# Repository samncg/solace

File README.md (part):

# Solace

A pocket-sized, battery-powered **hi-fi music player** built around the Raspberry Pi
**RP2350B**. Music files live on a microSD card, decode on the MCU, and go out through a
**PCM5102A** DAC and a **TPA6132A2** capless headphone amplifier to a 3.5 mm jack. A
2.83″ 200×648 SPI TFT shows the UI, a **DRV2605L** drives haptics, and an IMU, a magnetic
encoder and six buttons provide input. A **PCF8563TS** real-time clock keeps time on a
coin cell, and an **I²S MEMS microphone** supports capture and voice-driven mini-games.

This document is the project's single source of truth for **what the hardware is, how it
is put together, and what is still open**.

- **Status:** schematic complete and netlist-verified. **Board outline drafted, no placement yet.**
- **EDA:** KiCad 10.0
- **Intended build:** single-sided PCB (see [§14](#14-known-limitations--open-items))

---

## 1. Scope

**In scope**

- Portable, battery-powered audio playback (local files on microSD).
- 2.83″ colour display with software-adjustable brightness.
- Wired headphone/earbud output.
- Haptic feedback, motion sensing, rotary navigation (magnetic encoder), 6 tactile buttons.
- I²S MEMS microphone for capture and mini-games.
- Real-time clock with CR1220 backup (SMT holder, single-sided assembly).
- USB-C charging with power-path so the device runs while charging.
- Firmware-visible battery voltage, battery temperature, and charger state.

**Out of scope / not present**

- No speaker, no Bluetooth/Wi-Fi (no radio of any kind).
- No software in this repository — this is the hardware design only.
- No PCB layout beyond the drafted 100 × 64 mm outline (see [§14](#14-known-limitations--open-items)).

---

## 2. Repository layout

| Path | Contents |
|---|---|
| `main.kicad_sch` | The complete schematic (single flat sheet) |
| `main.kicad_pro` | KiCad project settings |
| `main.txt` | Netlist, `kicadsexpr` format — **generated**, do not hand-edit |
| `main.csv` | BOM — **generated/curated**, grouped by value + footprint |
| `main.kicad_pcb` | **Board file: 100 × 64 mm outline, 4-layer stackup.** No placement or routing yet |
| `docs/Solace_Hardware_Design_Documentation_RevB.pdf` | Design documentation package: architecture, electrical specification, interfaces, BOM appendix and the schematic as an A2 fold-out |
| `tools/build_docs.py` | Regenerates that PDF from `main.csv`, `main.txt` and `main.kicad_sch` |
| `libs/lcsc/` | Imported LCSC symbols, footprints and 3D models |
| `ganyu.kicad_sym`, `ganyu.kicad_mod` | Local custom symbol/footprint library |
| `docs/datasheets/rp2350/` | RP2350 datasheet + *Hardware design with RP2350* |
| `docs/datasheets/panels/` | Panel datasheets (C14 14-pin, H12 12-pin, CON8 8-pin variants) |
| `docs/mechanical/` | Enclosure sketch (`rough-sketch.png`, `.pdn`) |
| `fabrication/jlcpcb/` | JLCPCB fabrication output and project database |
| `fabrication/gerbers/` | Gerber and drill export plus job file |
| `backups/` | Manual schematic snapshots, earlier BOM/netlist, superseded PDFs |
| `backups/kicad-autosave/` | Timestamped KiCad auto-backup ZIPs |
| `backups/stray-main.kicad_pcb/` | Archived stray folder that previously shadowed the board filename |

> `main.kicad_pcb` currently contains **only the board outline** (Edge.Cuts, 100 × 64 mm,
> 3 mm corner radius) plus the 4-layer stackup. It has no footprints, so the first
> *Update PCB from Schematic* will drop in all 159 parts cleanly.

---

## 3. System architecture

```mermaid
graph TD
    USB["USB-C 16P<br/>CC 5.1k, USBLC6 ESD, 1.1A fuse"]
    CHG["TP4056 charger<br/>500 mA, CHRG#/STDBY# to MCU"]
    PROT["DW01A + FS8205A<br/>cell protection (BAT-)"]
    CELL["Li-ion cell<br/>JST-PH CN2"]
    LS["Load sharing<br/>D1 Schottky + Q4 PMOS"]
    VSYS["VSYS rail"]
    LDO1["AP2112K-3.3<br/>600 mA"]
    LDO2["TPS7A2033<br/>300 mA low-noise"]
    V3["+3V3 digital"]
    V3A["AUDIO_3V3"]
    MCU["RP2350B<br/>QFN-80"]
    FLASH["W25Q128JV<br/>16 MB QSPI flash"]
    PSRAM["APS6404L<br/>8 MB QSPI PSRAM"]
    SD["microSD<br/>TF-01A"]
    LCD["2.83in 200x648 TFT<br/>GC9B72, 4-wire SPI"]
    BL["Backlight<br/>Q2 + R35 3.3R, PWM"]
    DAC["PCM5102A<br/>I2S DAC"]
    AMP["TPA6132A2<br/>capless HP amp"]
    JACK["3.5 mm TRS jack"]
    HAP["DRV2605L<br/>haptics"]
    IMU["LSM6DSO<br/>IMU"]
    ENC["AS5600<br/>magnetic encoder"]
    EXP["TCA9554<br/>I2C GPIO expander"]
    BTN["6 buttons<br/>UP/DOWN/LEFT/RIGHT/A/B"]
    RTC["PCF8563TS<br/>I2C RTC + CR1220 backup"]
    MIC["I2S MEMS mic"]

    USB --> CHG
    USB -->|VSYS via D1| VSYS
    CHG --> CELL
    CELL --- PROT
    CELL -->|via Q4| VSYS
    VSYS --> LDO1 --> V3
    VSYS --> LDO2 --> V3A
    V3 --> MCU
    V3 --> FLASH
    V3 --> PSRAM
    V3 --> SD
    V3 --> LCD
    V3 --> HAP
    V3 --> IMU
    V3 --> ENC
    V3 --> EXP
    V3 --> RTC
    V3A --> DAC --> AMP --> JACK
    MCU <--> FLASH
    MCU <--> PSRAM
    MCU <--> SD
    MCU -->|SPI1| LCD
    MCU -->|PWM| BL
    MCU -->|I2S| DAC
    MCU <-->|I2C0| HAP
    MCU <-->|I2C0| IMU
    MCU <-->|I2C0| ENC
    MCU <-->|I2C0| EXP
    MCU <-->|I2C0| RTC
    MCU <-->|I2S PIO| MIC
    EXP --> BTN
```

---

## 4. Compute, memory, clock

| Item | Part | Notes |
|---|---|---|
| MCU | **RP2350B** (QFN-80), LCSC `C42415655` | All GPIOs 0–47 available |
| Program flash | **W25Q128JVSIQ** 128 Mbit (16 MB) QSPI, `U17` | Shares the QSPI bus |
| PSRAM | **APS6404L-3SQR** 64 Mbit (8 MB) QSPI, `U1` | Chip-select on **GPIO0** (`XIP_CS1n`), separate from flash CS |
| Crystal | **ABM8-272-T3** (12 MHz), `U18` | The Pico/Pico 2 crystal; 15 pF load caps `C61`/`C62`, 1 kΩ series `R23` |
| Core supply | RP2350 internal buck | 3.3 µH `AOTA-B201610S3R3-101-T` (`L10`) → `+1V1`, `C58` 10 µF + `C59` 1 µF |
| Regulator analog supply | `VREG_AVDD` | 33 Ω (`R41`) + 4.7 µF (`C60`), per the RP2350 reference design |

The core-rail network (inductor part number, `VREG_AVDD` RC filter) is copied **exactly**
from *Hardware design with RP2350* — including the Abracon inductor, which is a polarised
part. **Layout note:** the inductor's polarity dot must be oriented as in the reference
design, or regulator instability results.

**Debug:** `J3`, 3-pin SWD header (SWDIO/SWCLK/GND) + `SW12` BOOTSEL + `SW11` RUN.

---

## 5. Power

### 5.1 Topology

```
USB-C ──F3 1.1A──┬── TP4056 (U2) ──► BAT+ ──► cell (CN2)
                 │        │
                 │        └──► DW01A + FS8205A protection in the BAT- path
                 │
                 └──D1 (B5819WS)──► VSYS ◄──Q4 (AO3401A)── BAT+
                                       │
                                       ├── AP2112K-3.3 (U4) ──► +3V3  (digital)
                                       └── TPS7A2033 (U5)  ──► AUDIO_3V3 (audio)
```

### 5.2 Charger

| Parameter | Value |
|---|---|
| Charger | **TP4056** (`U2`), ESOP-8 |
| Charge current | **500 mA** (`R5` = 2.4 kΩ, I = 1200/R) |
| `CE` | Driven by `CHARGE_EN` (see below) |
| `CHRG#` | → **GPIO18**, 10 kΩ pull-up `R13`. Active-low: charging in progress |
| `STDBY#` | → **GPIO22**, 10 kΩ pull-up `R49`. Active-low: charge complete |
| `TEMP` | Tied to GND — the TP4056's own thermal cut-out is **disabled** |

### 5.3 Load sharing (power path)

`BAT+` feeds only the cell, the protection FETs, the charger and the fuel-gauge divider.
The system is fed from **`VSYS`**, which is whichever of USB or battery is present:

| Ref | Part | Role |
|---|---|---|
| `D1` | B5819WS Schottky | USB → `VSYS`, blocks battery back-feed into the USB port |
| `Q4` | AO3401A PMOS | `BAT+` → `VSYS`; **source on `VSYS`, drain on `BAT+`** so the body diode can never let USB charge the cell |
| `R44` | 100 Ω | Gate pull-up to `USB_5V` |
| `R45` | 100 kΩ | Gate pull-down |
| `C66` | 22 µF | `VSYS` bulk |
| `C67` | 10 µF | `BAT+` / charger output |

Behaviour: USB present → gate ≈ 5 V vs. a 4.65 V source, Vgs ≈ +0.35 V → **Q4 off**, cell
disconnected from the load, charger termination works correctly. USB absent → gate 0 V,
Vgs = −V<sub>BAT</sub> → **Q4 on**.

### 5.4 Regulators

| Rail | Regulator | Load |
|---|---|---|
| `+3V3` | AP2112K-3.3 (`U4`), 600 mA | MCU I/O, flash, PSRAM, SD, display, backlight, haptics, sensors, expander |
| `AUDIO_3V3` | TPS7A2033 (`U5`), 300 mA, low-noise | DAC + amplifier |

`AUDIO_3V3` is split per domain through ferrites `L5`–`L8` into the PCM5102A's `AVDD`,
`CPVDD`, `DVDD` and the amplifier's `VDD`.

**Power switch:** `SW5` (slide) connects `VSYS` to `LDO_ENABLE`, which drives both
regulators' `EN` pins; `R10` (100 kΩ) holds them off when the switch is open. The
regulators' inputs are always live, so only their quiescent current is drawn when "off".

### 5.5 Charger control (firmware)

`CE` is not tied to USB — firmware can stop charging:

```
USB_5V ──R47 10k──┬── U2.CE
                  └── Q5.D (AO3400A)   S → GND
                       G ──R48 100k── GND
                       G ── CHARGE_CTL ── GPIO21
```

| State | `CHARGE_CTL` | Q5 | `CE` | Charging |
|---|---|---|---|---|
| MCU off / power switch open | floating | off (R48) | 5 V via R47 | **enabled** |
| Boot, before init | high-Z | off | 5 V | **enabled** |
| Allow | driven low | off | 5 V | enabled |
| Cut | driven high | on | 0 V | **disabled** |

Fail-safe by construction: a dead MCU or a hung boot can never leave the device unable to
charge. The MCU pin only drives a gate, so 5 V never reaches the RP2350.

### 5.6 Battery monitoring

| Quantity | Sense | Notes |
|---|---|---|
| Pack voltage | `R24` 220 k / `R28` 100 k → **GPIO40 / ADC0**, `C25` 100 nF | 4.2 V → 1.31 V |
| Cell temperature | `J2` external NTC + `R46` 10 k to `+3V3`, `C68` 100 nF → **GPIO44 / ADC4** | 10 k NTC, B = 3950 |

Temperature is referenced to the regulated `+3V3`, so it reads correctly **whether or not
USB is connected**. The NTC is **off-board** (`J2`): it must be bonded to the cell, not
mounted on the PCB, and the 100 nF at the connector keeps the ADC stable over the lead
length.

---

## 6. Display

| Item | Value |
|---|---|
| Panel | **ZJY283-2064KIWPG03-C14** — 2.83″, 200×648, normally black, all-view |
| Driver IC | **GC9B72** |
| Interface | 4-wire SPI (write-only — no SDO, no TE on this variant) |
| Connector | `U9` **KH-FG0.5-H2.0-14P-SMT**, 14-pin 0.5 mm FPC, H = 2.0 mm, LCSC `C5441651` |
| FPC | 0.5 mm pitch, `PI+FPC = 0.3 ± 0.03 mm` |

| Panel pin | Signal | MCU |
|---|---|---|
| 1 | GND | — |
| 2 | RESET | GPIO7 |
| 3 | SCL | **GPIO10** (SPI1 SCK) |
| 4 | D/C | GPIO8 |
| 5 | CS | **GPIO9** (SPI1 CSn) |
| 6 | SDA | **GPIO11** (SPI1 TX) |
| 7 | NC | — |
| 8 | GND | — |
| 9 | VDD | `+3V3` |
| 10 | LEDK | backlight cathode |
| 11, 12 | GND | — |
| 13, 14 | NC | — |

SPI mode **0 or 3** (the panel latches SDA on the SCL rising edge). CS and RESET are
active-low. Hardware `SPI1` is used for all three of SCK/MOSI/CS.

**Local decoupling:** `C63` 1 µF at the panel's VDD pin.

### 6.1 Backlight

`+3V3` → (LED anodes, tied internally to VDD) → LEDK → `R35` **3.3 Ω** → `Q2` (AO3400A,
low-side) → GND. Gate on **GPIO6**, pulled down by `R36` 10 kΩ (default off).

Brightness is **PWM on GPIO6** — GPIO6's alternate function 4 is **PWM3 A**, so a hardware
PWM slice drives the gate directly. Use 10–20 kHz; average LED current ≈ duty × ~95 mA.

> **Backlight limitation — please read §14.1.** The C14 variant has **no LEDA pin**; the
> LED anodes are internally tied to VDD, so the string only ever sees 3.3 V against a
> V<sub>F</sub> of ≈3.0–3.2 V. Rated brightness (120 mA / 350 cd/m²) is **not reachable**
> from this rail.

---

## 7. Audio

```
RP2350 I2S ──► PCM5102A (U6) ──470R──► TPA6132A2 (U11) ──► PJ-342 jack (CN1)
 BCK  GPIO3      2.1 Vrms line out      capless, charge pump      3.5 mm TRS
 DIN  GPIO2                             G0/G1 = 0 (−6 dB)
 LRCK GPIO4
 XSMT GPIO42 (10k pull-down, starts muted)
 EN   GPIO43 (10k pull-down, starts off)
```

| Item | Value |
|---|---|
| DAC | **PCM5102A** (`U6`), I²S, 2.1 V<sub>rms</sub> |
| `SCK` (pin 12) | Tied to GND → internal clock derived from BCK |
| Charge pump | `C21` 2.2 µF across CAPP/CAPM, `C20` 2.2 µF on VNEG |
| Amp | **TPA6132A2** (`U11`), capless (integrated charge pump) |
| Amp supply | `AUDIO_3V3` via ferrite `L8` |
| Jack | **PJ-342** (`CN1`), 3.5 mm TRS |
| Rail | `AUDIO_3V3` from the low-noise TPS7A2033 |

**Jack wiring:** `CN1.2`/`CN1.5` = GND (sleeve tabs), `CN1.3` = right, `CN1.6` = left,
`CN1.4`/`CN1.7` = switch contacts (unused). Pad geometry is consistent with this, but the
symbol has generic pin names — **confirm TIP/RING with a continuity test** on a real part.

**Loudness:** comfortable. ~0.6 V<sub>rms</sub> into 16–32 Ω is ≈110–119 dB SPL on typical
earbuds. At the fixed −6 dB gain the DAC's 2.1 V<sub>rms</sub> becomes ≈1.05 V<sub>rms</sub>,
close to the TPA6132A2's maximum swing on a 3.3 V rail, so cap digital volume a few dB to
avoid clipping into 16 Ω.

**Gain:** `G0`/`G1` both strapped to GND = **−6 dB** (lowest setting). Per the TPA6132A2
table: `G0` high + `G1` low = 0 dB, `G0` low + `G1` high = +3 dB, both high = +6 dB.

---

## 8. Haptics

| Item | Value |
|---|---|
| Driver | **DRV2605L** (`U7`), I²C, `+3V3`, REG cap `C49` 1 µF |
| Actuator | **`J4`** 2-pin header (2.54 mm), nets `HAPTIC_A` / `HAPTIC_B` |
| Control | `EN` = GPIO1, `IN/TRIG` = GPIO5 |
| Local bulk | `C64` 22 µF at the driver (`+3V3`) |

`EN` has a 100 kΩ pull-down (`R43`) so the driver stays off until firmware configures
GPIO1, and `IN/TRIG` has a 100 kΩ pull-down (`R53`) so a floating pin cannot trigger it at
boot. Drive voltage equals `+3V3`, so use a 2–3 V LRA or ERM; a 5 V ERM would need a
boost.

---

## 9. Sensors and input

| Device | Ref | Bus | Notes |
|---|---|---|---|
| **LSM6DSO** IMU | `U8` | I²C `0x6A` | `SDO/SA0` = GND; `INT1` → **GPIO19** |
| **AS5600** magnetic encoder | `U12` | I²C `0x36` | `DIR` = GND; `OUT`/`PGO` unused |
| **TCA9554** I²C expander | `U14` | I²C `0x20` | 6 buttons on P0–P5; `#INT` → **GPIO20** (`BTN_INT`, `R38` pull-up) |
| **PCF8563TS** RTC | `U13` | I²C `0x51` | 32.768 kHz crystal `Y2`; `INT`/`CLKOUT` unused |
| microSD | `Card1` | SDIO | see §10 |

**I²C bus (`I2C0`)** — GPIO16 (SDA) / GPIO17 (SCL), 4.7 kΩ pull-ups `R12`/`R25`, shared by
IMU, encoder, haptics, expander **and** the `J1` expansion header.

**Buttons** (all to GND, read through the expander):

| Button | Expander pin | Net |
|---|---|---|
| UP | P0 | `BTN_UP` |
| DOWN | P1 | `BTN_DOWN` |
| LEFT | P2 | `BTN_LEFT` |
| RIGHT | P3 | `BTN_RIGHT` |
| A | P4 | `BTN_A` |
| B | P5 | `BTN_B` |

`J1` ("OLED_I2C", 4-pin): GND, `+3V3`, SCL, SDA (pins 1–4) — a spare I²C port for a
debug display.

### 9.1 Real-time clock

| Item | Value |
|---|---|
| Device | **PCF8563TS** (`U13`, TSSOP-8), I²C address `0x51` |
| Timebase | `Y2` 32.768 kHz crystal, load caps `C69`/`C70` 15 pF |
| Supply | `RTC_VDD` — diode-OR of `+3V3` and the backup cell |
| Backup | `U19` **KH-CR1220-2** CR1220 SMT holder (LCSC `C5365933`) via `D3` BAT54C dual Schottky |
| Local decoupling | `C71` 100 nF at the supply pin |

`D3` is wired as a diode-OR: anode 1 to `+3V3`, anode 2 to the cell, cathode to `RTC_VDD`.
The clock therefore runs from the regulated rail when the device is on and from the coin
cell when it is off — no switch-over logic, no firmware involvement. At RTC current
(sub-microamp) the Schottky drop is only tens of millivolts, so the backup path delivers
≈2.9 V, well inside the 1.0–5.5 V range. Because the cathode is common, neither source can
push current back into the other, so the coin cell is never charged.

`INT` and `CLKOUT` are left open, so time is read by polling the registers.

### 9.2 Microphone

| Item | Value |
|---|---|
| Device | **ICS-43434** I²S MEMS microphone (`U15`) |
| Bus | `MIC_BCLK` GPIO23, `MIC_WS` GPIO24, `MIC_DATA` GPIO25 |
| Channel | `LR` tied to GND (left channel) |
| Decoupling | `C72` 100 nF + `C73` 1 µF at the supply pin |
| Data line | `R50` 100 kΩ pull-down on `MIC_DATA` (discharges the line when `SD` tristates) |

The microphone has its **own** I²S pins rather than sharing the DAC's bus. That spends three
GPIOs that were otherwise free, but capture and playback stay independent, so both can run
at once without reconfiguring a shared PIO state machine. As with the DAC, the clocks come
from a PIO program — the RP2350 has no dedicated I²S peripheral.

The **acoustic port must align with an enclosure opening or gasket**; the MEMS element
senses through the port, not at the board surface. This part is **bottom-port**, and its
land pattern has a 0.4 mm through-hole for the port — so the acoustic path reaches the
underside of the PCB. Either put the enclosure aperture on the back, or bridge the hole to
a front aperture with a gasket.

---

## 10. Storage

`Card1` (TF-01A microSD) in 4-bit SDIO on arbitrary pins (PIO-friendly):

| SD signal | MCU |
|---|---|
| DAT0 | GPIO12 |
| DAT1 | GPIO13 |
| DAT2 | GPIO14 |
| DAT3 / CS | GPIO15 |
| CMD | GPIO39 |
| CLK | GPIO41 |

Card-detect (`Card1.9`) is unconnected; insertion must be detected in software (or add a
GPIO later — see [§14](#14-known-limitations--open-items)).

---

## 11. GPIO map (RP2350B)

| GPIO | Pin | Function | Net |
|---|---|---|---|
| 0 | 77 | PSRAM chip select | `XIP_CS1n` |
| 1 | 78 | Haptics enable | `RP2354_GPIO1` → `U7.EN` |
| 2 | 79 | I2S data (DIN) | `RP2354_GPIO2` → `U6.DIN` |
| 3 | 80 | I2S bit clock (BCK) | `RP2354_GPIO3` → `U6.BCK` |
| 4 | 1 | I2S word clock | `RP2354_GPIO4` → `U6.LRCK` |
| 5 | 2 | Haptic trigger | `RP2354_GPIO5` → `U7.IN/TRIG` |
| 6 | 3 | **LCD backlight (PWM3A)** | `RP2354_GPIO6` |
| 7 | 4 | LCD reset | `RP2354_GPIO7` |
| 8 | 6 | LCD D/C | `RP2354_GPIO8` |
| 9 | 7 | **LCD CS (SPI1 CSn)** | `RP2354_GPIO9` |
| 10 | 8 | **LCD SCL (SPI1 SCK)** | `RP2354_GPIO10` |
| 11 | 9 | **LCD SDA (SPI1 TX)** | `RP2354_GPIO11` |
| 12 | 11 | SD DAT0 | `RP2354_GPIO12` |
| 13 | 12 | SD DAT1 | `RP2354_GPIO13` |
| 14 | 13 | SD DAT2 | `RP2354_GPIO14` |
| 15 | 14 | SD DAT3 | `RP2354_GPIO15` |
| 16 | 16 | **I²C0 SDA** | `RP2354_GPIO16` |
| 17 | 17 | **I²C0 SCL** | `RP2354_GPIO17` |
| 18 | 18 | Charger CHRG# (low = charging) | `RP2354_GPIO18` |
| 19 | 19 | IMU INT1 | `RP2354_GPIO19` |
| 20 | 20 | Button expander #INT | `BTN_INT` |
| 21 | 21 | **Charger enable (high = stop)** | `CHARGE_CTL` |
| 22 | 22 | Charger STDBY# (low = complete) | `CHARGE_STAT` |
| 23 | 23 | **Mic bit clock** | `MIC_BCLK` → `U15` |
| 24 | 25 | **Mic word clock** | `MIC_WS` → `U15` |
| 25 | 26 | **Mic data** | `MIC_DATA` ← `U15` |
| 26–38 | — | **free** | — |
| 39 | 48 | SD CMD | `RP2354_GPIO39` |
| 40 | 49 | **ADC0** — battery voltage | `RP2354_GPIO40` |
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
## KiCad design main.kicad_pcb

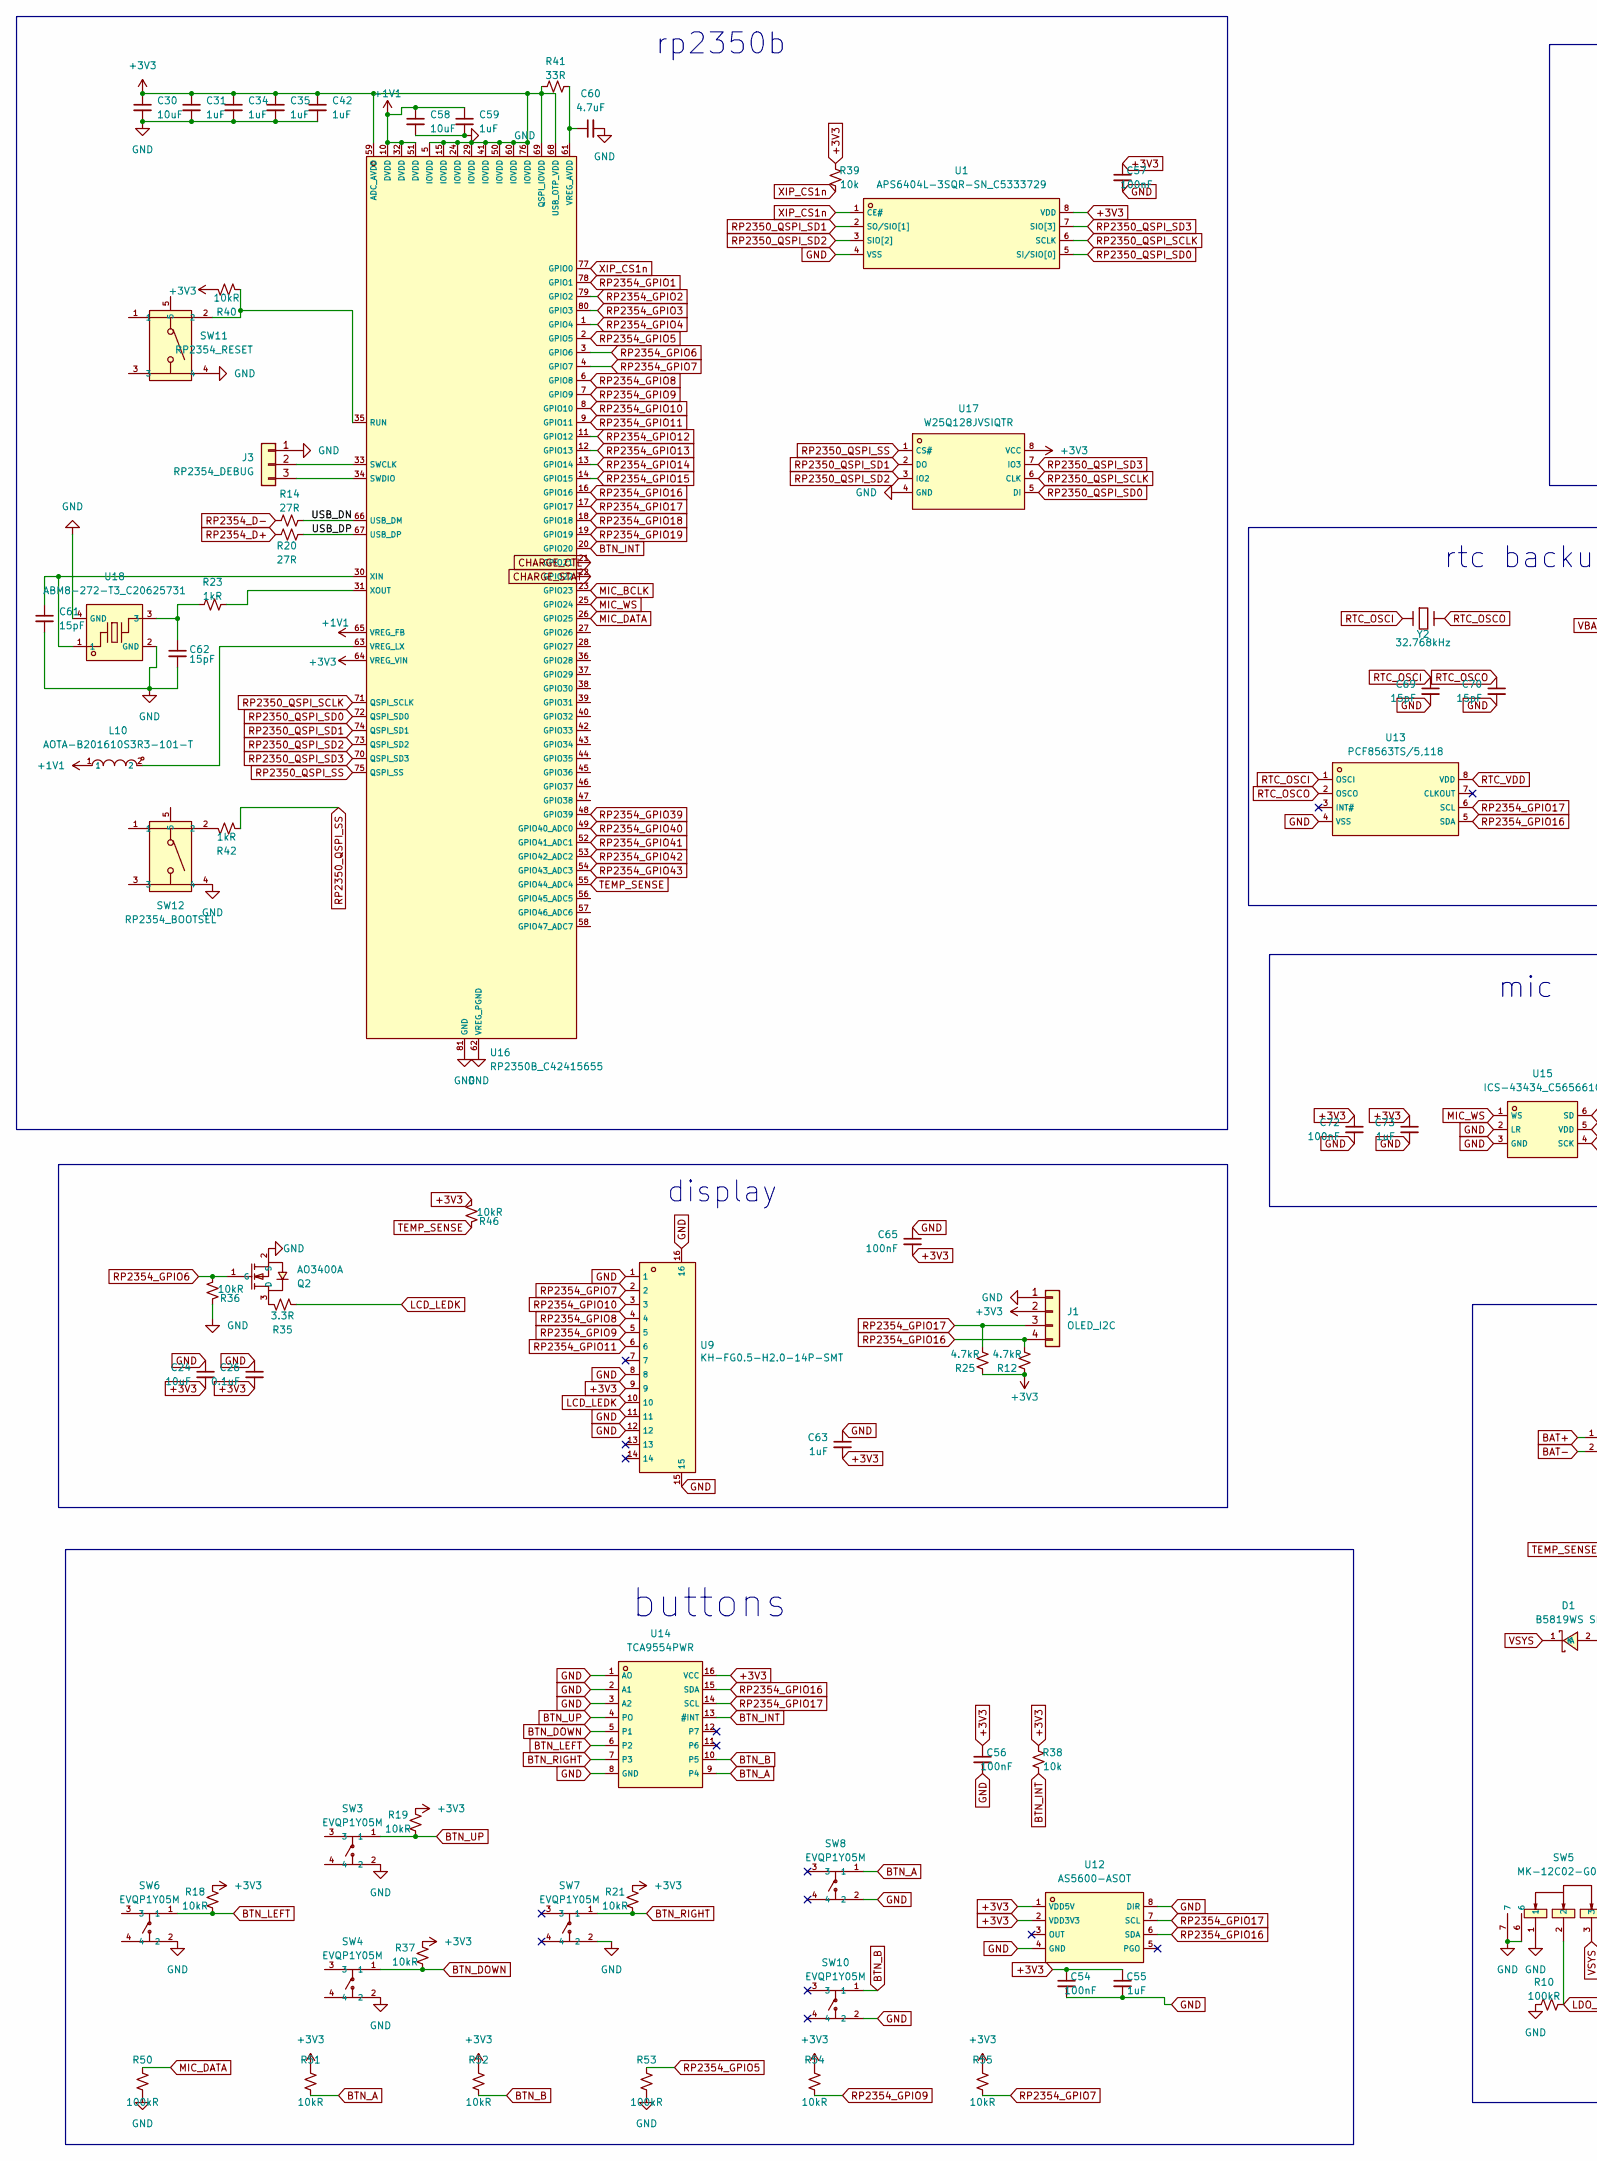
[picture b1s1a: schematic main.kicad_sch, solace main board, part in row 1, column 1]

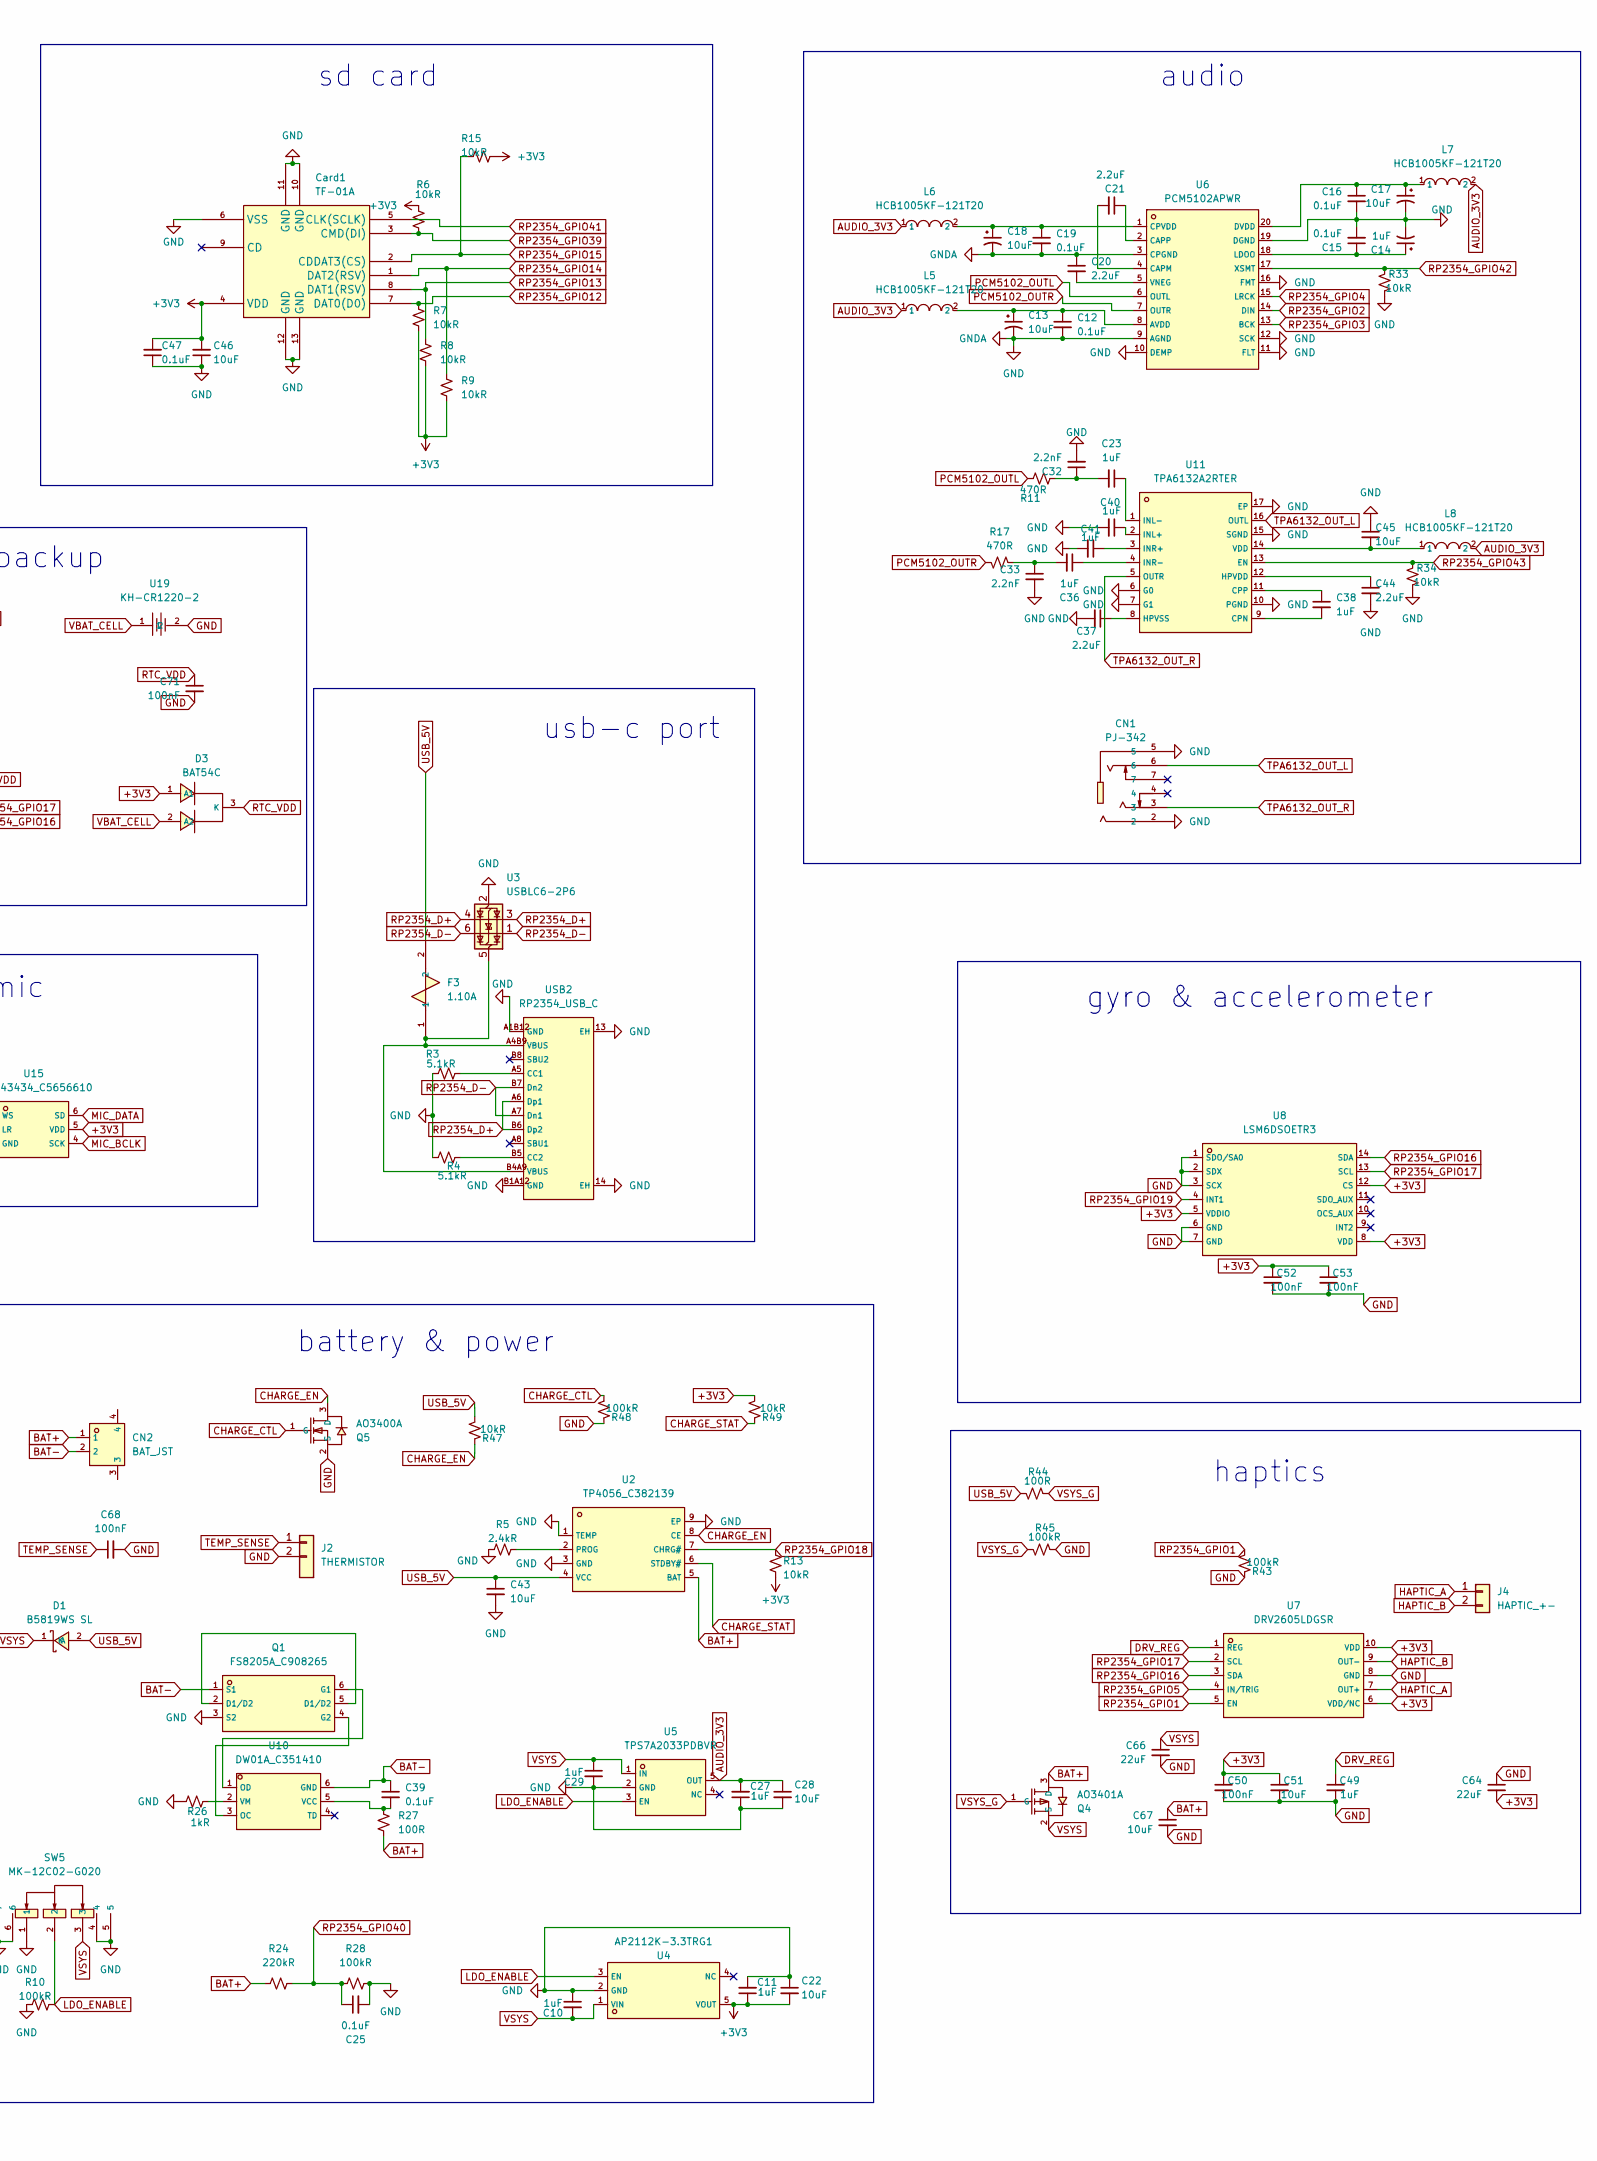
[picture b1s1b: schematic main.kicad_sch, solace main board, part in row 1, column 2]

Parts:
C10, C11, C23, C27, C29, C31, C34, C35, C36, C38, C40, C41, C42, C49, C55, C59, C63, C73: 1uF; C_0603_1608Metric
C12, C15, C16, C19, C25, C26, C39, C47: 0.1uF; C_0603_1608Metric
C13, C17, C18: 10uF; CP_EIA-3216-18_Kemet-A
C14: 1uF; CP_EIA-3216-18_Kemet-A
C20, C21, C37, C44: 2.2uF; C_0603_1608Metric
C22, C24, C28, C30, C43, C45, C46, C51, C58, C67: 10uF; C_0805_2012Metric
C32, C33: 2.2nF; C_0603_1608Metric
C50, C52, C53, C54, C56, C57, C65, C68, C71, C72: 100nF; C_0603_1608Metric
C60: 4.7uF; C_0603_1608Metric
C61, C62, C69, C70: 15pF; C_0603_1608Metric
C64, C66: 22uF; C_0805_2012Metric
CN1: PJ-342; C668606_AUDIO-SMD_PJ-342_C668606; LCSC C668606
CN2: BAT_JST; C295747_CONN-SMD_P2_00_S2B-PH-SM4-TB-LF-SN; LCSC C295747
Card1: TF-01A; C91145_TF-SMD_TF-01A; LCSC C91145
D1: B5819WS SL; C22624_SOD-323_L1_8-W1_3-LS2_5-RD; LCSC C22624
D3: BAT54C; C2135_SOT-23-3_L2_9-W1_6-P1_90-LS2_8-BR; LCSC C2135
F3: 1.10A; C20801_F1206; LCSC C20801
J1: OLED_I2C; PinHeader_1x04_P2.54mm_Vertical
J2: THERMISTOR; PinHeader_1x02_P2.54mm_Vertical
J3: RP2354_DEBUG; PinHeader_1x03_P2.54mm_Vertical
J4: HAPTIC_+-; PinHeader_1x02_P2.54mm_Vertical
L5, L6, L7, L8: HCB1005KF-121T20; C141722_L0402; LCSC C141722
L10: AOTA-B201610S3R3-101-T; C42411119_IND-SMD_L2_0-W1_6_AOTA-B201610S3R3-101-T; LCSC C42411119
Q1: FS8205A_C908265; C908265_SOT-23-6_L2_9-W1_6-P0_95-LS2_8-BR; LCSC C908265
Q2, Q5: AO3400A; C20917_SOT-23-3_L2_9-W1_3-P1_90-LS2_4-BR; LCSC C20917
Q4: AO3401A; C15127_SOT-23_L2_9-W1_3-P1_90-LS2_4-BR; LCSC C15127
R3, R4: 5.1kR; R_0603_1608Metric
R5: 2.4kR; R_0603_1608Metric
R6, R7, R8, R9, R13, R15, R18, R19, R21, R33, R34, R36, R37, R40, R46, R47, R49, R51, R52, R54, R55: 10kR; R_0603_1608Metric
R10, R28, R43, R45, R48, R50, R53: 100kR; R_0603_1608Metric
R11, R17: 470R; R_0603_1608Metric
R12, R25: 4.7kR; R_0603_1608Metric
R14, R20: 27R; R_0603_1608Metric
R23, R26, R42: 1kR; R_0603_1608Metric
R24: 220kR; R_0603_1608Metric
R27, R44: 100R; R_0603_1608Metric
R35: 3.3R; R_0603_1608Metric
R38, R39: 10k; R_0603_1608Metric
R41: 33R; R_0603_1608Metric
SW3, SW4, SW6, SW7, SW8, SW10: EVQP1Y05M; C2915186_SW-SMD_4P-L6_1-W6_0-P4_50-LS7_4; LCSC C2915186
SW5: MK-12C02-G020; C963206_SW-SMD_MK-12C02-G020; LCSC C963206
SW11: RP2354_RESET; C72443_KEY-SMD_KMR2XXGXXX; LCSC C72443
SW12: RP2354_BOOTSEL; C72443_KEY-SMD_KMR2XXGXXX; LCSC C72443
U1: APS6404L-3SQR-SN_C5333729; C5333729_SOIC-8_L4_9-W3_9-P1_27-LS6_0-BL; LCSC C5333729
U2: TP4056_C382139; C382139_ESOP-8_L4_9-W3_9-P1_27-LS6_0-BL-EP; LCSC C382139
U3: USBLC6-2P6; SOT-666
U4: AP2112K-3.3TRG1; C51118_SOT-25-5_L2_9-W1_6-P0_95-LS2_8-BL; LCSC C51118
U5: TPS7A2033PDBVR; C2862740_SOT-23-5_L2_9-W1_6-P0_95-LS2_8-BR; LCSC C2862740
U6: PCM5102APWR; C107671_TSSOP-20_L6_5-W4_4-P0_65-LS6_4-BL; LCSC C107671
U7: DRV2605LDGSR; C527464_VSSOP-10_L3_0-W3_0-P0_50-LS4_9-BL; LCSC C527464
U8: LSM6DSOETR3; C5122483_LGA-14L_L3_0-W2_5-P0_50-TL; LCSC C5122483
U9: KH-FG0.5-H2.0-14P-SMT; C5441651_FPC-SMD_14P-P0_50_KINGHELM_KH-FG0_5-H2_0-14P-SMT; LCSC C5441651
U10: DW01A_C351410; C351410_SOT-23-6_L2_9-W1_6-P0_95-LS2_8-BL; LCSC C351410
U11: TPA6132A2RTER; C69901_WQFN-16_L3_0-W3_0-P0_50-TL-EP1_6; LCSC C69901
U12: AS5600-ASOT; C499458_SOIC-8_L5_0-W4_0-P1_27-LS6_0-BL; LCSC C499458
U13: PCF8563TS/5,118; C27397_TSSOP-8_L3_0-W3_0-P0_65-LS4_9-BL; LCSC C27397
U14: TCA9554PWR; C477924_TSSOP-16_L5_0-W4_4-P0_65-LS6_4-TL; LCSC C477924
U15: ICS-43434_C5656610; C5656610_MIC-SMD_6P-L3_5-W2_7-P0_90-BL; LCSC C5656610
U16: RP2350B_C42415655; C42415655_QFN-80_L10_0-W10_0-P0_40-TL-EP3_4; LCSC C42415655
U17: W25Q128JVSIQTR; C97521_SOIC-8_L5_3-W5_3-P1_27-LS8_0-BL; LCSC C97521
U18: ABM8-272-T3_C20625731; C20625731_CRYSTAL-SMD_4P-L3_2-W2_5-BL; LCSC C20625731
U19: KH-CR1220-2; C5365933_BAT-SMD_CR1220-2; LCSC C5365933
USB2: RP2354_USB_C; C2765186_USB-C-SMD_TYPE-C-16PIN-2MD-073; LCSC C2765186
Y2: 32.768kHz; Crystal_SMD_3215-2Pin_3.2x1.5mm

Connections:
+1V1: C58.1, C59.1, L10.1, U16.10 (DVDD), U16.32 (DVDD), U16.51 (DVDD), U16.65 (VREG_FB)
+3V3: C11.1, C22.2, C24.2, C26.2, C30.1, C31.1, C34.1, C35.1, C42.1, C46.2, C47.2, C50.1, C51.1, C52.1, C53.1, C54.1, C55.1, C56.1, C57.1, C63.2, C64.2, C65.2, C72.1, C73.1, Card1.4 (VDD), D3.1 (A1), J1.2, R6.1, R7.2, R8.2, R9.2, R12.1, R13.2, R15.2, R18.2, R19.2, R21.2, R25.1, R37.2, R38.1, R39.1, R40.1, R41.1, R46.2, R49.2, R51.1, R52.1, R54.1, R55.1, U1.8 (VDD), U4.5 (VOUT), U7.6 (VDD/NC), U7.10 (VDD), U8.5 (VDDIO), U8.8 (VDD), U8.12 (CS), U9.9, U12.1 (VDD5V), U12.2 (VDD3V3), U14.16 (VCC), U15.5 (VDD), U16.5 (IOVDD), U16.15 (IOVDD), U16.24 (IOVDD), U16.29 (IOVDD), U16.41 (IOVDD), U16.50 (IOVDD), U16.59 (ADC_AVDD), U16.60 (IOVDD), U16.64 (VREG_VIN), U16.68 (USB_OTP_VDD), U16.69 (QSPI_IOVDD), U16.76 (IOVDD), U17.8 (VCC)
/USB_DN: R14.2, U16.66 (USB_DM)
/USB_DP: R20.2, U16.67 (USB_DP)
AUDIO_3V3: C27.2, C28.1, L5.1, L6.1, L7.2, L8.2, U5.5 (OUT)
BAT+: C67.1, CN2.1, Q4.3 (D), R24.1, R27.2, U2.5 (BAT)
BAT-: C39.1, CN2.2, Q1.1 (S1), U10.6 (GND)
BTN_A: R51.2, SW8.1, U14.9 (P4)
BTN_B: R52.2, SW10.1, U14.10 (P5)
BTN_DOWN: R37.1, SW4.1, U14.5 (P1)
BTN_INT: R38.2, U14.13 (#INT), U16.20 (GPIO20)
BTN_LEFT: R18.1, SW6.1, U14.6 (P2)
BTN_RIGHT: R21.1, SW7.1, U14.7 (P3)
BTN_UP: R19.1, SW3.1, U14.4 (PO)
CHARGE_CTL: Q5.1 (G), R48.2, U16.21 (GPIO21)
CHARGE_EN: Q5.3 (D), R47.1, U2.8 (CE)
CHARGE_STAT: R49.1, U2.6 (STDBY#), U16.22 (GPIO22)
DRV_REG: C49.1, U7.1 (REG)
GND: C10.1, C11.2, C12.2, C13.2, C14.2, C15.2, C16.2, C17.2, C18.2, C19.2, C20.1, C22.1, C24.1, C25.2, C26.1, C27.1, C28.2, C29.2, C30.2, C31.2, C32.2, C33.2, C34.2, C35.2, C37.2, C40.2, C41.2, C42.2, C43.2, C44.2, C45.1, C46.1, C47.1, C49.2, C50.2, C51.2, C52.2, C53.2, C54.2, C55.2, C56.2, C57.2, C58.2, C59.2, C60.2, C61.2, C62.2, C63.1, C64.1, C65.1, C66.2, C67.2, C68.2, C69.2, C70.2, C71.2, C72.2, C73.2, CN1.2, CN1.5, Card1.6 (VSS), Card1.10 (GND), Card1.11 (GND), Card1.12 (GND), Card1.13 (GND), J1.1, J2.2, J3.1, Q1.3 (S2), Q2.2 (S), Q5.2 (S), R3.2, R4.2, R5.1, R10.1, R26.2, R28.2, R33.1, R34.1, R36.1, R43.1, R45.1, R48.1, R50.2, R53.2, SW3.2, SW4.2, SW5.1, SW5.4, SW5.5, SW5.6, SW5.7, SW6.2, SW7.2, SW8.2, SW10.2, SW11.4, SW12.4, U1.4 (VSS), U2.1 (TEMP), U2.3 (GND), U2.9 (EP), U3.2 (GND), U4.2 (GND), U5.2 (GND), U6.3 (CPGND), U6.9 (AGND), U6.10 (DEMP), U6.11 (FLT), U6.12 (SCK), U6.16 (FMT), U6.19 (DGND), U7.8 (GND), U8.1 (SDO/SA0), U8.2 (SDX), U8.3 (SCX), U8.6 (GND), U8.7 (GND), U9.1, U9.8, U9.11, U9.12, U9.15, U9.16, U11.6 (G0), U11.7 (G1), U11.10 (PGND), U11.15 (SGND), U11.17 (EP), U12.4 (GND), U12.8 (DIR), U13.4 (VSS), U14.1 (AO), U14.2 (A1), U14.3 (A2), U14.8 (GND), U15.2 (LR), U15.3 (GND), U16.62 (VREG_PGND), U16.81 (GND), U17.4 (GND), U18.2 (GND), U18.4 (GND), U19.2, USB2.13 (EH), USB2.14 (EH), USB2.A1B12 (GND), USB2.B1A12 (GND)
HAPTIC_A: J4.1, U7.7 (OUT+)
HAPTIC_B: J4.2, U7.9 (OUT-)
LCD_LEDK: R35.2, U9.10
LDO_ENABLE: R10.2, SW5.2, U4.3 (EN), U5.3 (EN)
MIC_BCLK: U15.4 (SCK), U16.23 (GPIO23)
MIC_DATA: R50.1, U15.6 (SD), U16.26 (GPIO25)
MIC_WS: U15.1 (WS), U16.25 (GPIO24)
unnamed: C23.2, C32.1, R11.1
unnamed: C33.1, C36.2, R17.1
unnamed: C62.1, R23.1, U18.3
unnamed: J3.2, U16.33 (SWCLK)
unnamed: J3.3, U16.34 (SWDIO)
unnamed: Q1.2 (D1/D2), Q1.5 (D1/D2)
unnamed: Q1.6 (G1), U10.1 (OD)
unnamed: Q1.4 (G2), U10.3 (OC)
unnamed: Q2.3 (D), R35.1
unnamed: R42.1, SW12.2
unnamed: R5.2, U2.2 (PROG)
unnamed: F3.1, U3.5 (VBUS), USB2.A4B9 (VBUS), USB2.B4A9 (VBUS)
unnamed: C12.1, C13.1, L5.2, U6.8 (AVDD)
unnamed: C21.2, U6.4 (CAPM)
unnamed: C21.1, U6.2 (CAPP)
unnamed: C18.1, C19.1, L6.2, U6.1 (CPVDD)
unnamed: C16.1, C17.1, L7.1, U6.20 (DVDD)
unnamed: C14.1, C15.1, U6.18 (LDOO)
unnamed: C20.2, U6.5 (VNEG)
unnamed: C39.2, R27.1, U10.5 (VCC)
unnamed: R26.1, U10.2 (VM)
unnamed: C38.2, U11.9 (CPN)
unnamed: C38.1, U11.11 (CPP)
unnamed: C44.1, U11.12 (HPVDD)
unnamed: C37.1, U11.8 (HPVSS)
unnamed: C40.1, U11.2 (INL+)
unnamed: C23.1, U11.1 (INL-)
unnamed: C41.1, U11.3 (INR+)
unnamed: C36.1, U11.4 (INR-)
unnamed: C45.2, L8.1, U11.14 (VDD)
unnamed: R40.2, SW11.2, U16.35 (RUN)
unnamed: C60.1, R41.2, U16.61 (VREG_AVDD)
unnamed: L10.2, U16.63 (VREG_LX)
unnamed: C61.1, U16.30 (XIN), U18.1
unnamed: R23.2, U16.31 (XOUT)
unnamed: R3.1, USB2.A5 (CC1)
unnamed: R4.1, USB2.B5 (CC2)
PCM5102_OUTL: R11.2, U6.6 (OUTL)
PCM5102_OUTR: R17.2, U6.7 (OUTR)
RP2350_QSPI_SCLK: U1.6 (SCLK), U16.71 (QSPI_SCLK), U17.6 (CLK)
RP2350_QSPI_SD0: U1.5 (SI/SIO[0]), U16.72 (QSPI_SD0), U17.5 (DI)
RP2350_QSPI_SD1: U1.2 (SO/SIO[1]), U16.74 (QSPI_SD1), U17.2 (DO)
RP2350_QSPI_SD2: U1.3 (SIO[2]), U16.73 (QSPI_SD2), U17.3 (IO2)
RP2350_QSPI_SD3: U1.7 (SIO[3]), U16.70 (QSPI_SD3), U17.7 (IO3)
RP2350_QSPI_SS: R42.2, U16.75 (QSPI_SS), U17.1 (CS#)
RP2354_D+: R20.1, U3.3 (I/O2), U3.4 (I/O2), USB2.A6 (Dp1), USB2.B6 (Dp2)
RP2354_D-: R14.1, U3.1 (I/O1), U3.6 (I/O1), USB2.A7 (Dn1), USB2.B7 (Dn2)
RP2354_GPIO1: R43.2, U7.5 (EN), U16.78 (GPIO1)
RP2354_GPIO2: U6.14 (DIN), U16.79 (GPIO2)
RP2354_GPIO3: U6.13 (BCK), U16.80 (GPIO3)
RP2354_GPIO4: U6.15 (LRCK), U16.1 (GPIO4)
RP2354_GPIO5: R53.1, U7.4 (IN/TRIG), U16.2 (GPIO5)
RP2354_GPIO6: Q2.1 (G), R36.2, U16.3 (GPIO6)
RP2354_GPIO7: R55.2, U9.2, U16.4 (GPIO7)
RP2354_GPIO8: U9.4, U16.6 (GPIO8)
RP2354_GPIO9: R54.2, U9.5, U16.7 (GPIO9)
RP2354_GPIO10: U9.3, U16.8 (GPIO10)
RP2354_GPIO11: U9.6, U16.9 (GPIO11)
RP2354_GPIO12: Card1.7 (DAT0(D0)), R7.1, U16.11 (GPIO12)
RP2354_GPIO13: Card1.8 (DAT1(RSV)), R8.1, U16.12 (GPIO13)
RP2354_GPIO14: Card1.1 (DAT2(RSV)), R9.1, U16.13 (GPIO14)
RP2354_GPIO15: Card1.2 (CDDAT3(CS)), R15.1, U16.14 (GPIO15)
RP2354_GPIO16: J1.4, R12.2, U7.3 (SDA), U8.14 (SDA), U12.6 (SDA), U13.5 (SDA), U14.15 (SDA), U16.16 (GPIO16)
RP2354_GPIO17: J1.3, R25.2, U7.2 (SCL), U8.13 (SCL), U12.7 (SCL), U13.6 (SCL), U14.14 (SCL), U16.17 (GPIO17)
RP2354_GPIO18: R13.1, U2.7 (CHRG#), U16.18 (GPIO18)
RP2354_GPIO19: U8.4 (INT1), U16.19 (GPIO19)
RP2354_GPIO39: Card1.3 (CMD(DI)), R6.2, U16.48 (GPIO39)
RP2354_GPIO40: C25.1, R24.2, R28.1, U16.49 (GPIO40_ADC0)
RP2354_GPIO41: Card1.5 (CLK(SCLK)), U16.52 (GPIO41_ADC1)
RP2354_GPIO42: R33.2, U6.17 (XSMT), U16.53 (GPIO42_ADC2)
RP2354_GPIO43: R34.2, U11.13 (EN), U16.54 (GPIO43_ADC3)
RTC_OSCI: C69.1, U13.1 (OSCI), Y2.1
RTC_OSCO: C70.1, U13.2 (OSCO), Y2.2
RTC_VDD: C71.1, D3.3 (K), U13.8 (VDD)
TEMP_SENSE: C68.1, J2.1, R46.1, U16.55 (GPIO44_ADC4)
TPA6132_OUT_L: CN1.6, U11.16 (OUTL)
TPA6132_OUT_R: CN1.3, U11.5 (OUTR)
USB_5V: C43.1, D1.2 (A), F3.2, R44.2, R47.2, U2.4 (VCC)
VBAT_CELL: D3.2 (A2), U19.1
VSYS: C10.2, C29.1, C66.1, D1.1 (K), Q4.2 (S), SW5.3, U4.1 (VIN), U5.1 (IN)
VSYS_G: Q4.1 (G), R44.1, R45.2
XIP_CS1n: R39.2, U1.1 (CE#), U16.77 (GPIO0)

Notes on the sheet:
display
mic
battery & power
haptics
sd card
audio
gyro & accelerometer
usb-c port
rtc backup
rp2350b
buttons

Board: 4 copper layers, 159 parts (0 on the bottom side), 108 nets, no tracks yet.

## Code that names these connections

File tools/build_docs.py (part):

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    st.append(TBL([["Parameter", "Value", "Reference"],
                   ["Charger IC", "TP4056, ESOP-8", "U2"],
                   ["Programmed current", "500 mA (R5 = 2.4 kohm, I = 1200 / R)", "R5"],
                   ["Status outputs", "CHRG# to GPIO18, STDBY# to GPIO22", "both active low, open drain"],
                   ["Status pull-ups", "10 kohm to +3V3", "R13, R49"],
                   ["Enable", "CHARGE_EN (see 4.5)", "Q5, R47, R48"],
                   ["Temperature sense", "TEMP tied to GND - internal cut-out disabled", "see 4.6"]],
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    st.append(P("CE is not tied to USB. It is pulled up to USB_5V by R47, so charging is enabled by default, "
                "and an N-channel MOSFET Q5 can pull it low to stop charging. The MCU drives only Q5's gate; "
                "5 V never reaches an RP2350 pin."))
    st.append(TBL([["Condition", "CHARGE_CTL (GPIO21)", "Q5", "CE", "Charging"],
                   ["MCU off, power switch open", "floating", "off (R48)", "5 V", "enabled"],
                   ["Boot, before firmware init", "high impedance", "off", "5 V", "enabled"],
                   ["Firmware allows", "driven low", "off", "5 V", "enabled"],
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    st.append(TBL([["Ref", "Device", "Function", "Notes"],
                   ["U16", "RP2350B, QFN-80", "Host MCU", "Dual Cortex-M33, external QSPI boot"],
                   ["U17", "W25Q128JVSIQ", "Program and asset storage", "128 Mbit = 16 MB, QSPI, chip select 0"],
                   ["U1", "APS6404L-3SQR-SN", "PSRAM", "64 Mbit = 8 MB, QSPI, chip select 1 on GPIO0"],
                   ["U18", "ABM8-272-T3", "12 MHz main crystal", "15 pF load caps C61/C62, 1 k series R23"],
                   ["L10", "AOTA-B201610S3R3-101-T", "Core buck inductor", "3.3 uH, polarised - observe the dot"]],
                  [36, 130, 118, CW - 284]))
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    st.append(H2("6.2  Signal assignment"))
    st.append(TBL([["Panel pin", "Signal", "MCU", "Note"],
                   ["1", "GND", "-", ""],
                   ["2", "RESET", "GPIO7", "active low"],
                   ["3", "SCL", "GPIO10", "SPI1 SCK"],
                   ["4", "D/C", "GPIO8", "command / data"],
                   ["5", "CS", "GPIO9", "SPI1 CSn, active low"],
                   ["6", "SDA", "GPIO11", "SPI1 TX, latched on SCL rising edge"],
                   ["7", "NC", "-", ""],
                   ["8", "GND", "-", ""],
                   ["9", "VDD", "+3V3", "panel maximum"],
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    st.append(H2("6.3  Backlight and brightness control"))
    st.append(P("The C14 variant exposes only the LED cathode. The LED anodes are tied internally to the "
                "panel's VDD, so the string is powered from +3V3 and the current is set by R35 in series "
                "with the low-side switch Q2. Brightness is set by PWM on the gate: GPIO6's alternate "
                "function 4 is PWM3 A, so a hardware PWM slice drives Q2 directly at a recommended 10 to "
                "20 kHz."))
    st.append(TBL([["Duty", "Average LED current", "Approximate luminance", "Note"],
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                   ["L8", "Ferrite", "AUDIO_3V3 to amplifier VDD", ""]],
                  [36, 96, 128, CW - 260]))
    st.append(Spacer(1, 6))
    st.append(P("Signal path: RP2350 I2S (BCK GPIO3, DIN GPIO2, LRCK GPIO4) into the DAC; DAC outputs are "
                "AC-coupled through 1 uF into the amplifier's differential inputs; amplifier outputs drive "
                "the jack directly. XSMT (GPIO42) and the amplifier enable (GPIO43) both carry 10 kohm "
                "pull-downs, so the chain starts muted and the amplifier starts off."))
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    st.append(H1("8  Haptics"))
    st.append(TBL([["Parameter", "Value"],
                   ["Driver", "DRV2605L, I2C, powered from +3V3"],
                   ["Actuator", "J4 2-pin header, nets HAPTIC_A / HAPTIC_B"],
                   ["Control", "EN on GPIO1, IN/TRIG on GPIO5"],
                   ["Local bulk", "C64 22 uF at the driver supply"],
                   ["Enable default", "R43 100 kohms pull-down on EN - driver off until firmware configures it"],
                   ["Trigger default", "R53 100 kohms pull-down on IN/TRIG - no trigger while GPIO5 floats"]],
                  [110, CW - 110]))
    st.append(P("Drive voltage equals +3V3, so the actuator must be a 2 to 3 V LRA or ERM. A 5 V ERM would "
                "require a boost converter that is not fitted."))
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    # ================================================== 9 sensors
    st.append(H1("9  Sensors and user input"))
    st.append(H2("9.1  I2C bus"))
    st.append(P("A single I2C0 bus on GPIO16 (SDA) and GPIO17 (SCL) with 4.7 kohm pull-ups carries every "
                "peripheral plus the J1 expansion header."))
    st.append(TBL([["Device", "Ref", "Address", "Notes"],
                   ["LSM6DSO IMU", "U8", "0x6A", "SDO/SA0 tied low; INT1 to GPIO19"],
                   ["AS5600 magnetic encoder", "U12", "0x36", "DIR tied low; OUT and PGO unused"],
                   ["TCA9554 expander", "U14", "0x20", "A0-A2 tied low; INT to GPIO20"],
                   ["DRV2605L haptics", "U7", "0x5A", "REG cap C49 1 uF"],
                   ["PCF8563TS real-time clock", "U13", "0x51", "32.768 kHz crystal, coin-cell backup"],
                   ["J1 expansion header", "J1", "-", "4-pin: GND, +3V3, SCL, SDA"]],
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
    st.append(H2("9.2  Buttons"))
    st.append(P("Six tactile switches connect to the expander with the common side to ground; the expander's "
                "open-drain interrupt reports changes on GPIO20, so no MCU pin is consumed per button."))
    st.append(TBL([["Button", "Switch", "Expander pin", "Net"],
                   ["Up", "SW3", "P0", "BTN_UP"],
                   ["Down", "SW4", "P1", "BTN_DOWN"],
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                   ["B", "SW10", "P5", "BTN_B"]],
                  [80, 70, 100, CW - 250]))
    st.append(P("The power switch SW5 is a slide switch in the regulator enable path, not a load switch: the "
                "regulator inputs remain at VSYS and only their enable pins are switched, with R10 holding "
                "them off. Reset is SW11 to the RP2350 RUN pin; BOOTSEL is SW12 via R42.", "cap"))

    st.append(H2("9.3  Real-time clock"))
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    st.append(H2("9.4  Microphone"))
    st.append(TBL([["Parameter", "Value"],
                   ["Device", "ICS-43434 I2S MEMS microphone (U15)"],
                   ["Data path", "MIC_BCLK GPIO23, MIC_WS GPIO24, MIC_DATA GPIO25"],
                   ["Channel select", "LR tied to GND (left channel)"],
                   ["Decoupling", "C72 100 nF and C73 1 uF at the supply pin"],
                   ["Data line", "R50 100 kohms pull-down on MIC_DATA (line discharge)"]],
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    st.append(P("The microSD socket (TF-01A) is wired for 4-bit SDIO on freely assigned GPIOs, which suits a "
                "PIO-based SDIO host or a bit-banged implementation. Card detect is not connected."))
    st.append(TBL([["SD signal", "MCU pin", "Note"],
                   ["DAT0", "GPIO12", ""],
                   ["DAT1", "GPIO13", ""],
                   ["DAT2", "GPIO14", ""],
                   ["DAT3 / CS", "GPIO15", ""],
                   ["CMD", "GPIO39", ""],
                   ["CLK", "GPIO41", "shares an ADC pin, unused as analogue"]],
                  [100, 90, CW - 190]))

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        ("Display moved from 8 to 14 pins", "The C14 panel replaced the earlier 8-pin FPC; connector U13 was "
         "removed and U9 wired to the C14 pin table."),
        ("SPI moved to hardware SPI1", "The earlier pin choice could not be served by a single SPI "
         "peripheral, since GPIO6 belongs to SPI0 and GPIO8 to SPI1."),
        ("Separate audio regulator", "Keeps the analogue rail away from the MCU's switching core supply and "
         "the PWM backlight."),
        ("RTC backup is a diode-OR", "A BAT54C from +3V3 and the coin cell needs no switch-over logic and "
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        "Keep D3, C71 and U19 together at the RTC supply pin, and keep the coin-cell holder away from the board edge.",
        "Mount the MEMS microphone so its acoustic port aligns with an enclosure opening; keep C72 and C73 within a few millimetres of the supply pin and do not route signals beneath the port.",
        "The ICS-43434 is a bottom-port microphone: the acoustic path is through the 0.4 mm hole in the land pattern, so the enclosure aperture must open onto the underside of the board or a gasket must bridge it.",
        "Keep the AUDIO_3V3 ferrites close to the DAC and amplifier pins.",
        "Single-sided build: confirm the FPC connector, USB-C receptacle and SD socket are all reachable from the back face.",
    ]))

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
